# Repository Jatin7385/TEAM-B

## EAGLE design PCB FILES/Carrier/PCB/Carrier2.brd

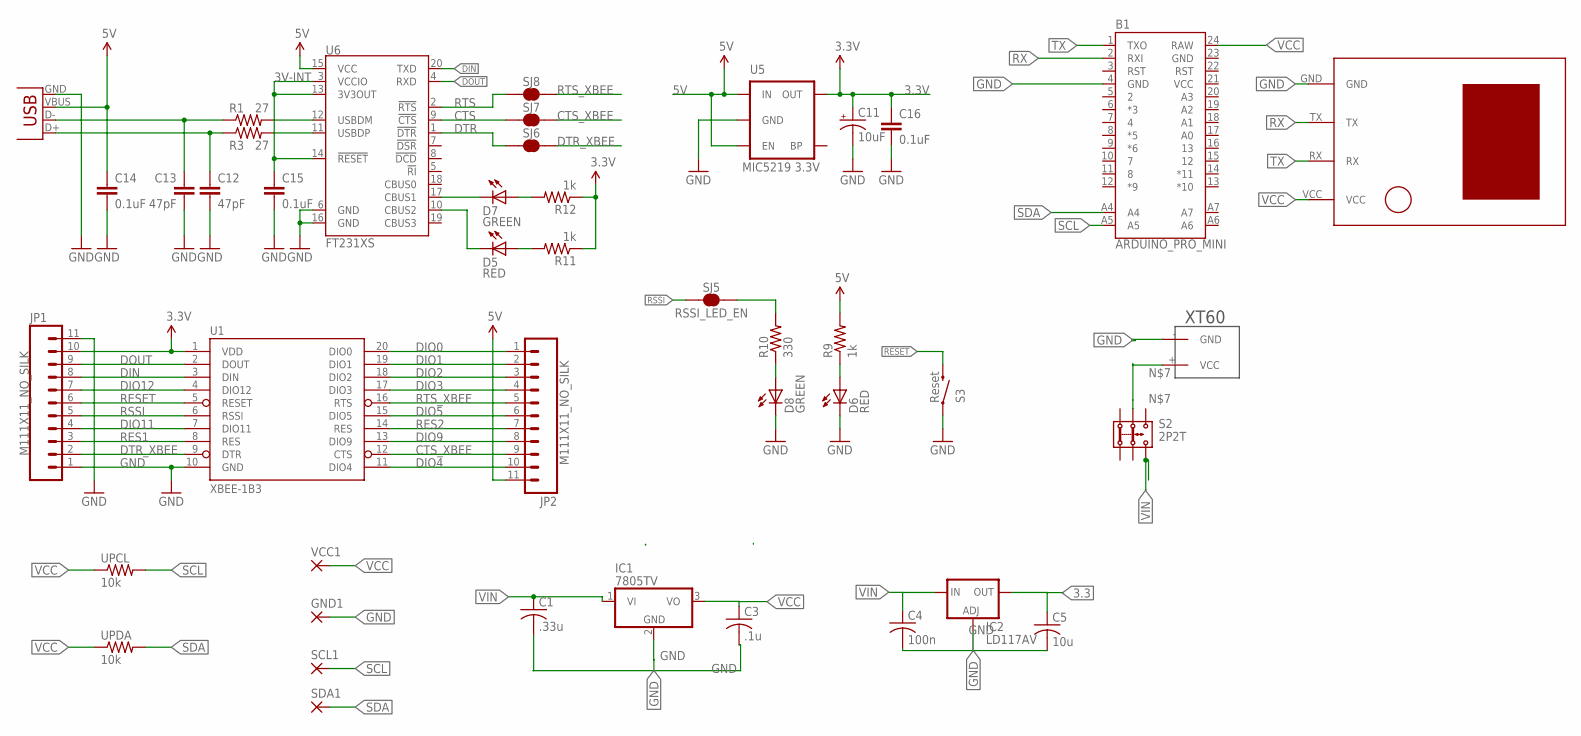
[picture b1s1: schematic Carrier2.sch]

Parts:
B1: ARDUINO_PRO_MINI
C1: .33u; C0805
C3: .1u; C0805
C4: 100n; C0805
C5: 10u; C0805
C11: 10uF; EIA3216
C12, C13: 47pF; 0603-CAP
C14, C15, C16: 0.1uF; 0603-CAP
D5, D6: RED; LED-0603
D7, D8: GREEN; LED-0603
GND1: 2,15/1,0
IC1: 7805TV; TO220V
IC2: LD117AV; TO220L1
JP1, JP2: M111X11_NO_SILK; 1X11_NO_SILK
R1, R3: 27; 0603-RES
R9, R11, R12: 1k; 0603-RES
R10: 330; 0603-RES
S2: 2P2T
S3: Reset; TACTILE_SWITCH_SMD
SCL1: 2,15/1,0
SDA1: 2,15/1,0
SJ5: RSSI_LED_EN; SJ_2S-TRACE
SJ6: DTR; SJ_2S-TRACE
SJ7: RTS_EN; SJ_2S-TRACE
SJ8: CTS_EN; SJ_2S-TRACE
U1: XBEE-1B3; XBEE-SMD
U5: MIC5219 3.3V; SOT23-5
U6: FT231XS; SSOP20_L
U$1: U-BLOX-NEO6V2
U$3: XT60
UPCL: 10k; M0805
UPDA: 10k; M0805
VCC1: 2,15/1,0
X2: USBSMD; USB-MINIB

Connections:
3.3V: C11.A (+), C16.1, JP1.10, R11.1, R12.1, U1.1 (VDD), U5.5 (OUT)
3V-INT: C15.1, U6.3 (VCCIO), U6.13 (3V3OUT), U6.14 (!RESET)
5V: C14.1, JP2.11, R9.2, U5.1 (IN), U5.3 (EN), U6.15 (VCC), X2.VBUS
CTS: SJ7.1, U6.9 (!CTS)
CTS_XBEE: JP2.9, SJ7.2, U1.12 (CTS)
DIN: JP1.8, U1.3 (DIN), U6.20 (TXD)
DIO0: JP2.1, U1.20 (DIO0)
DIO1: JP2.2, U1.19 (DIO1)
DIO2: JP2.3, U1.18 (DIO2)
DIO3: JP2.4, U1.17 (DIO3)
DIO4: JP2.10, U1.11 (DIO4)
DIO5: JP2.6, U1.15 (DIO5)
DIO9: JP2.8, U1.13 (DIO9)
DIO11: JP1.4, U1.7 (DIO11)
DIO12: JP1.7, U1.4 (DIO12)
DOUT: JP1.9, U1.2 (DOUT), U6.4 (RXD)
DTR: SJ6.1, U6.1 (!DTR)
DTR_XBEE: JP1.2, SJ6.2, U1.9 (DTR)
GND: B1.4 (GND), B1.23 (GND), C1.2, C3.2, C4.2, C5.2, C11.C (-), C12.2, C13.2, C14.2, C15.2, C16.2, D6.C, D8.C, GND1.1, IC1.2 (GND), IC2.1 (ADJ), JP1.1, JP1.11, S3.1, U1.10 (GND), U5.2 (GND), U6.6 (GND), U6.16 (GND), U$1.GND, U$3.- (GND), X2.GND
unnamed: C4.1, IC2.3 (IN)
unnamed: C3.1, IC1.3 (VO)
unnamed: C5.1, IC2.2 (OUT)
unnamed: S2.2.1, U$3.+ (VCC)
unnamed: D6.A, R9.1
unnamed: D5.A, R11.2
unnamed: D7.A, R12.2
unnamed: D8.A, R10.1
unnamed: D7.C, U6.17 (CBUS1)
unnamed: C12.1, R3.1, X2.D+
unnamed: C13.1, R1.1, X2.D-
unnamed: R3.2, U6.11 (USBDP)
unnamed: R1.2, U6.12 (USBDM)
unnamed: R10.2, SJ5.2
RES1: JP1.3, U1.8 (RES)
RES2: JP2.7, U1.14 (RES)
RESET: JP1.6, S3.3 (2), U1.5 (RESET)
RSSI: JP1.5, SJ5.1, U1.6 (RSSI)
RTS: SJ8.1, U6.2 (!RTS)
RTS_XBEE: JP2.5, SJ8.2, U1.16 (RTS)
RX: B1.2 (RXI), U$1.TX
SCL: B1.A5, SCL1.1, UPCL.2
SDA: B1.A4, SDA1.1, UPDA.2
TX: B1.1 (TXO), U$1.RX
TXLED1: D5.C, U6.10 (CBUS2)
VCC: B1.21 (VCC), B1.24 (RAW), U$1.VCC, UPCL.1, UPDA.1, VCC1.1
VIN: C1.1, IC1.1 (VI), S2.3.2

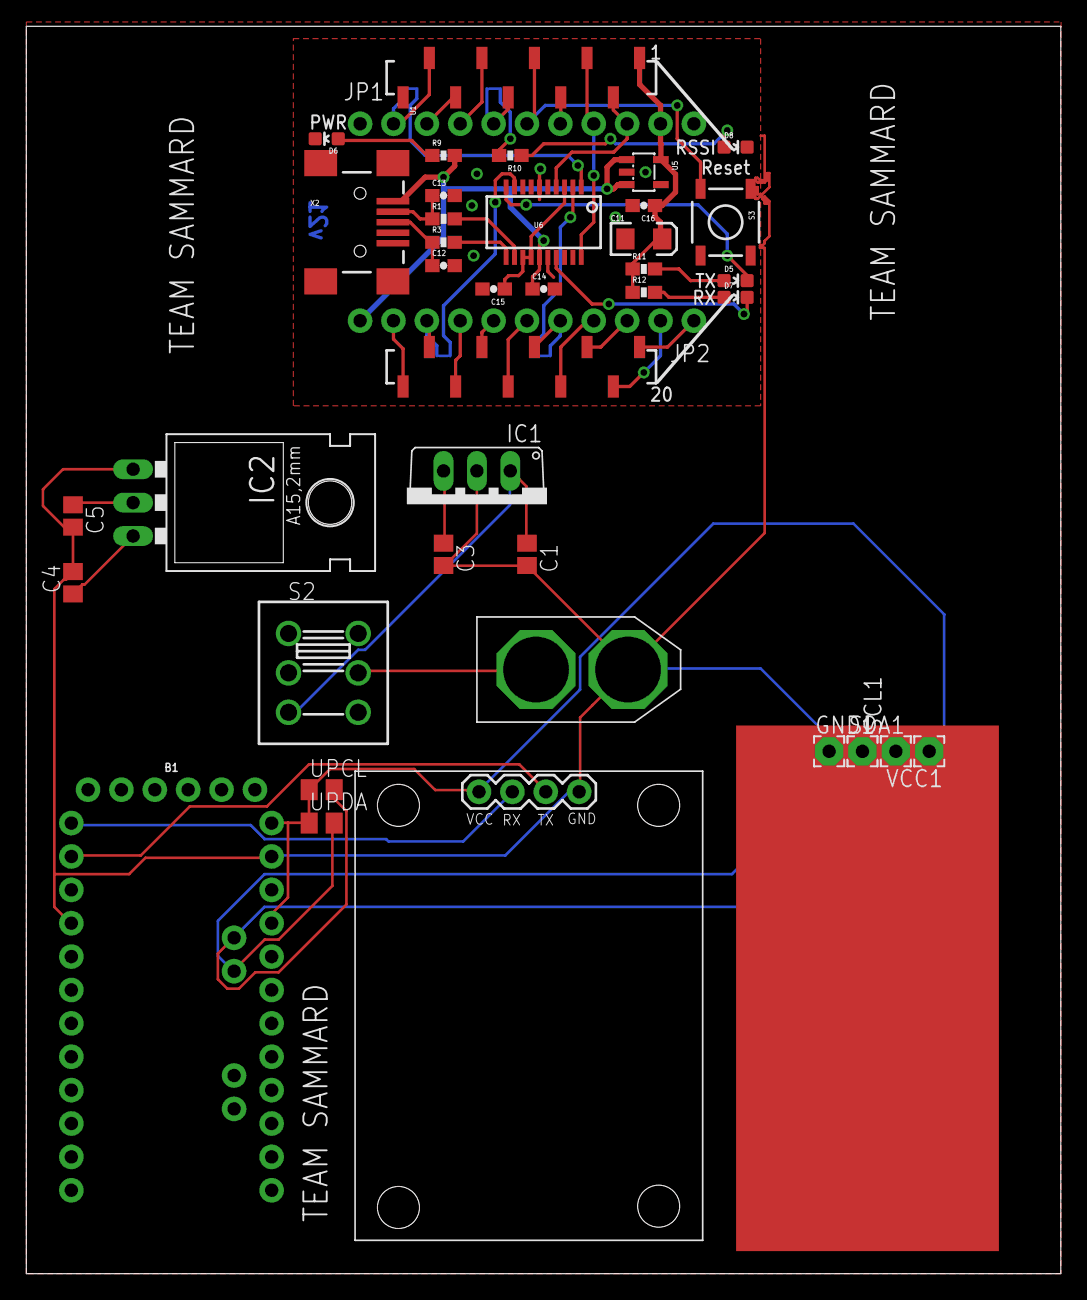
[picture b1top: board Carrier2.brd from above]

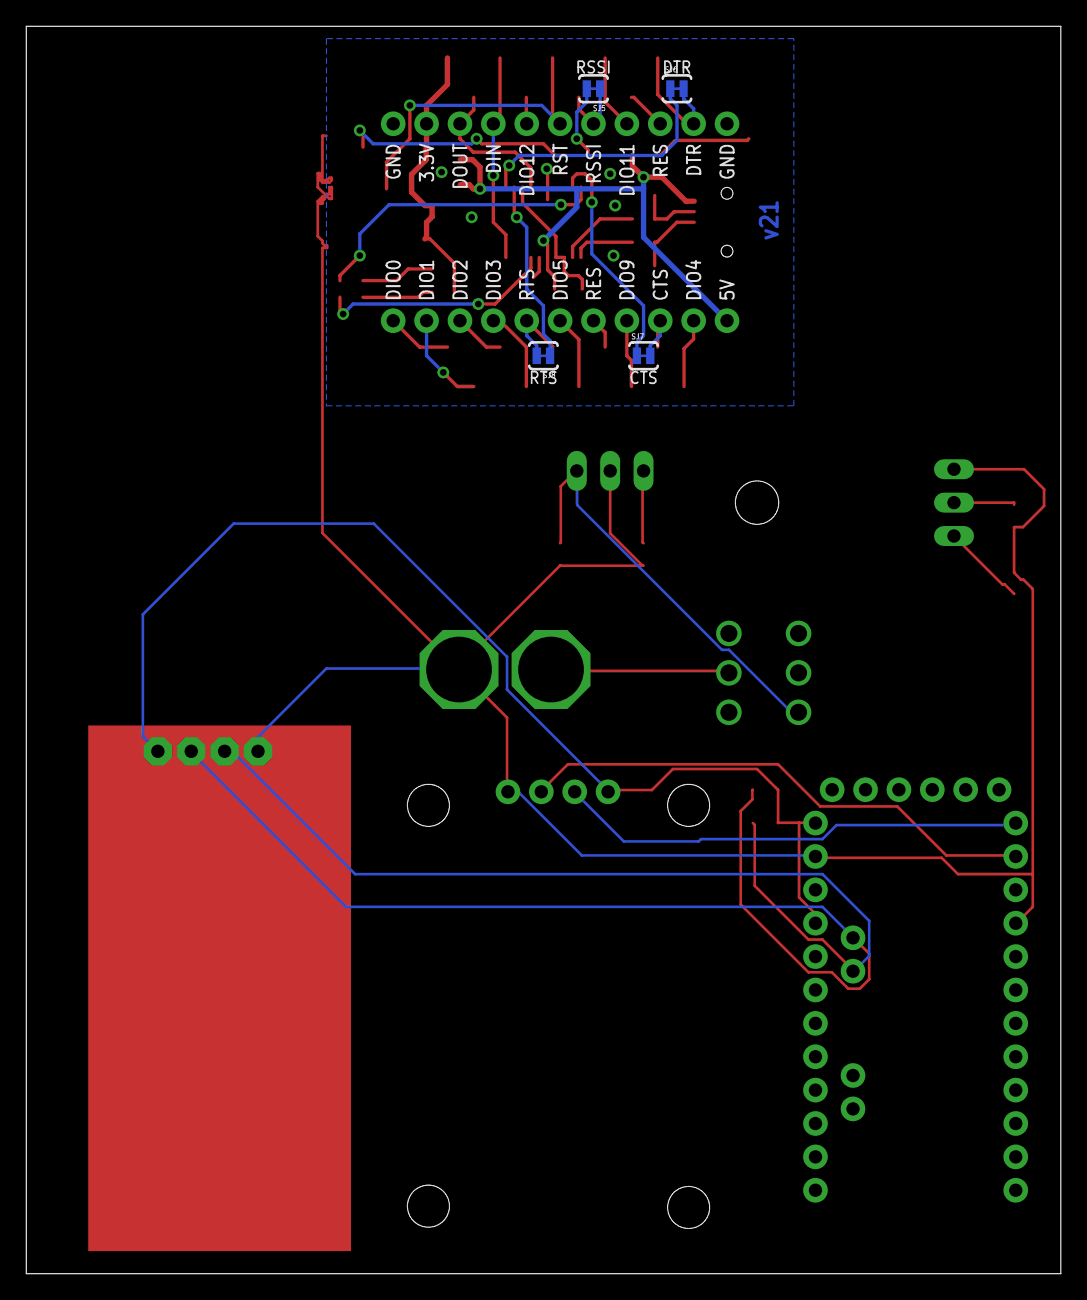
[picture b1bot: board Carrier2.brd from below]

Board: 2 copper layers, 78.7 x 94.9 mm, 43 parts (4 on the bottom side), 46 nets.

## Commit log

2021-05-20 Initial Commit FSW
2021-05-20 initial commit PCB
2021-05-20 Initial Commit GUI
2021-05-20 Initial Commit GCS
2021-05-21 updated
    mistakes
2021-05-21 deleted
    extra
2021-05-21 edited
    extra

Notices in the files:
parts and their libraries:
SparkFun-Boards: Licensing: Creative Commons ShareAlike 4.0 International - https://creativecommons.org/licenses/by-sa/4.0
SparkFun-DigitalIC: Licensing: CC v3.0 Share-Alike You are welcome to use this library for commercial purposes.
